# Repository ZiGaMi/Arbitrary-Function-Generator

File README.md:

# Arbitrary-Function-Generator
This repository contains of KiCad schematic and layout files, RTL code for iCE40 FPGA, C code for STM32F031K6 MCU and python script for software configuration of function generator.  

## Description
DAC: 12-bit R-2R ladder\
Output voltage: 3.3V\
SC current: 3.3mA

### Modes
Sinus: up to 1MHz\
Square: up to 100kHz\
Triange: up to 100kHz\
Saw: up to 100kHz\
Arbitrary: TBD

## Pics

work still in process...

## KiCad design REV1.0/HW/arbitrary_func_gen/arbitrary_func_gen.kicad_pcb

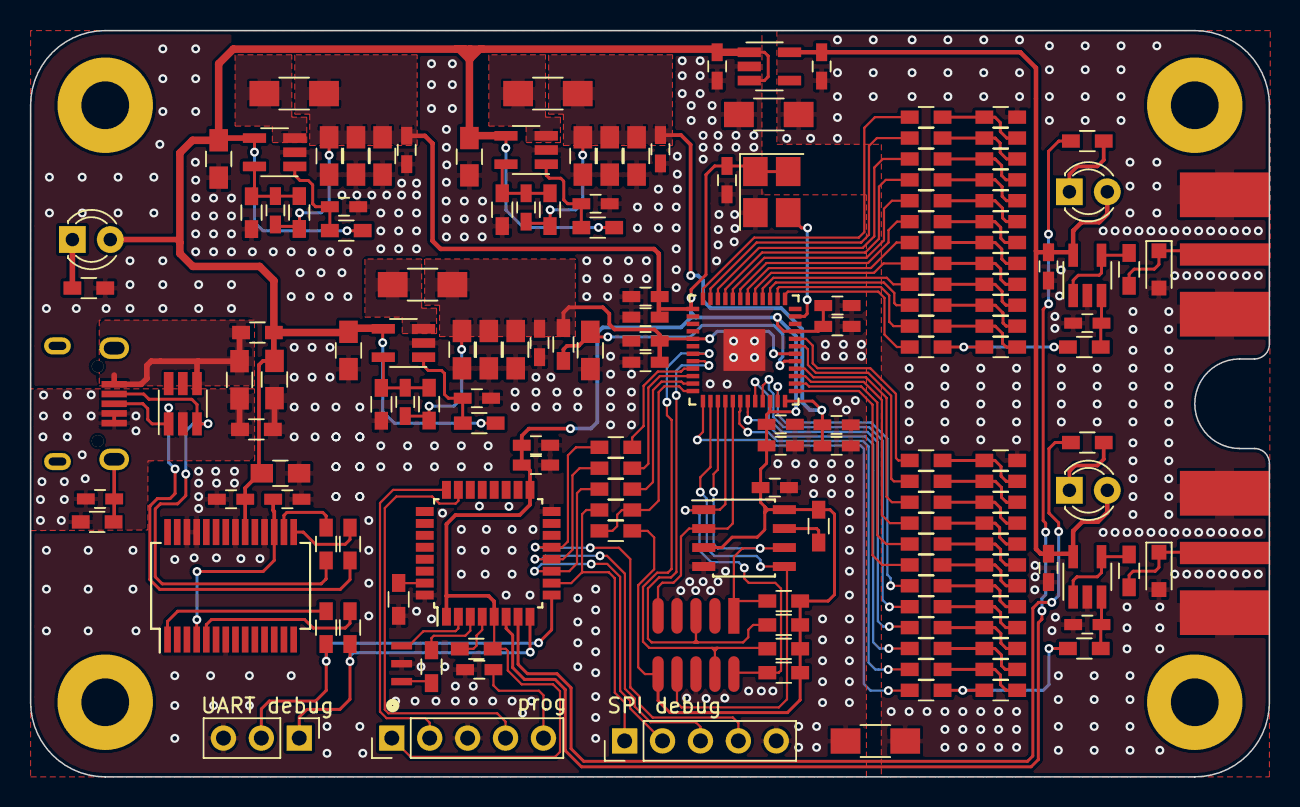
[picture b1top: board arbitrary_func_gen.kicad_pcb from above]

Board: 2 copper layers, 83.0 x 50.0 mm, 168 parts (0 on the bottom side), 111 nets.

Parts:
C1: 1n; C_0603_HandSoldering
C2, C3, C27, C46: 4u7; C_0805_HandSoldering
C4, C5, C15, C16, C17, C39, C49: 1u; C_0603_HandSoldering
C6, C7, C8, C18, C19, C20, C21, C22, C23, C24, C25, C26: 10u; C_0805_HandSoldering
C9, C12, C13, C14: DNS; C_0603_HandSoldering
C10, C11, C30, C31, C34, C35, C37, C40, C42, C44, C45, C47, C48: 100n; C_0603_HandSoldering
C28, C29, C32, C33, C36, C38, C41, C43: 10n; C_0603_HandSoldering
D1, D3, D4: LED; LED_D3.0mm_FlatTop
D2, D5: PESD3V3U1UA; D_SOD-323_HandSoldering
H1, H2, H3, H4: MountingHole_3.2mm_M3_Pad
J1: 629105150521_WE; USBMicro_629105150521_WE
J2: iCE40ProgPins; 2x5pin-R1.27mm
J3, J4: Conn_01x05; Pin_Header_Straight_1x05_Pitch2.54mm
J5, J6: SMA-J-P-H-ST-EM1; SMA_Coaxsial_EdgeBoard_Connector
J7: Conn_01x03; Pin_Header_Straight_1x03_Pitch2.54mm
L1, L2: BLM18PG471SH1D; L_0603_HandSoldering
L3, L4, L5: 2.2u; L_1206_HandSoldering
L6, L7: 22nH; L_0603_HandSoldering
R1: 1M; R_0603_HandSoldering
R2: 0R; R_1206_HandSoldering
R3: 0R; R_0603_HandSoldering
R4, R5, R13, R14, R15, R16, R17, R77: 10k; R_0603_HandSoldering
R6, R7, R8, R10: 150k; R_0603_HandSoldering
R9, R71, R72: 47k; R_0603_HandSoldering
R11: 33k; R_0603_HandSoldering
R12, R73, R74: 100R; R_0603_HandSoldering
R18, R43, R68, R75, R76, R78, R79, R80, R81: 1k; R_0603_HandSoldering
R19, R20, R21, R22, R23, R24, R25, R26, R27, R28, R29, R30, R42, R44, R45, R46, R47, R48, R49, R50, R51, R52, R53, R54, R55, R67: 22k; R_0603_HandSoldering
R31, R32, R33, R34, R35, R36, R37, R38, R39, R40, R41, R56, R57, R58, R59, R60, R61, R62, R63, R64, R65, R66: 11k; R_0603_HandSoldering
R69, R70: 27R; R_0603_HandSoldering
R82: DNS; R_1206_HandSoldering
R83: 680R; R_0603_HandSoldering
U1: IEC5LP1K-QFN48; QFP-48_7x7_Pitch0.5mm
U2: STM32F031K6Tx; LQFP-32_7x7mm_Pitch0.8mm
U3: FT232RL; SSOP-28_5.3x10.2mm_Pitch0.65mm
U4: LN1134; SOT-23-5_HandSoldering
U5, U7, U8: TLV62568DBV; SOT-23-5_HandSoldering
U6: SRV05-4; SOT-23-6_Handsoldering
U9: IS25LQ040B; SOIC-8_3.9x4.9mm_Pitch1.27mm
U10, U11: LT6220; SOT-23-5_HandSoldering
X1: ASFL1-25.000MHZ-EC-T; Oscillator_SMD_Abracon_ASE-4pin_3.2x2.5mm_HandSoldering
Y1: CSTCE8M00G15L99-R0; Crystal_Murata3Pin

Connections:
+1V2: C12.1, C15.1, C18.1, C21.1, C24.1, C29.1, C31.1, L3.2, R6.1, R12.2, U1.5, U1.30
+2V5: C13.1, C16.1, C19.1, C22.1, C25.1, C33.1, C35.1, L4.2, R8.1, U1.24
+3.3VA: C5.1, C40.1, C42.1, D3.2, D4.2, U4.5, U10.5, U11.5
+3V3: C14.1, C17.1, C20.1, C23.1, C26.1, C28.1, C30.1, C32.1, C34.1, C36.1, C37.1, C38.1, C39.2, C48.2, C49.2, J2.6, J3.1, L5.2, R10.1, R13.1, R14.1, R15.1, R16.1, R17.1, R71.1, R77.1, U1.1, U1.22, U1.33, U2.1, U2.5, U2.17, U9.3, U9.8, X1.1, X1.4
+5V: C3.1, C4.1, C6.1, C7.1, C8.1, C45.2, C46.2, D1.2, L1.2, R3.1, R4.1, R5.1, U3.20, U4.1, U4.3, U5.4, U7.4, U8.4
/FPGA/CDONE: J2.9, R13.2, U1.7
/FPGA/CLK_25MHZ: U1.35, X1.3
/FPGA/CRESET: J2.3, R14.2, U1.8
/FPGA/FLASH_CS: J2.10, R16.2, U1.16, U9.1
/FPGA/FLASH_MISO: J2.7, U1.14, U9.5
/FPGA/FLASH_MOSI: J2.5, U1.17, U9.2
/FPGA/FLASH_SCK: J2.1, R15.2, U1.15, U9.6
/MCU/CH1_LED: R78.2, U2.6
/MCU/CH2_LED: R79.2, U2.7
/MCU/CS_DBG: J4.1, R75.2, U2.10
/MCU/MISO_DBG: J4.3, R80.2, U2.12
/MCU/MOSI_DBG: J4.4, R81.2, U2.13
/MCU/NRST: C47.1, J3.5, R71.2, U2.4
/MCU/SCK_DBG: J4.2, R76.2, U2.11
/MCU/SWCLK: J3.2, U2.24
/MCU/SWDIO: J3.4, U2.23
/MCU/UART_RX: J7.2, R73.1, U2.9
/MCU/UART_TX: J7.1, R74.1, U2.8
BUSGND: C1.1, C2.2, J1.4, J1.5, L2.1, R1.2, U6.2
CH1_BIT_0: R30.2, U1.48
CH1_BIT_1: R29.2, U1.47
CH1_BIT_2: R28.2, U1.46
CH1_BIT_3: R27.2, U1.45
CH1_BIT_4: R26.2, U1.44
CH1_BIT_5: R25.2, U1.43
CH1_BIT_6: R24.2, U1.42
CH1_BIT_7: R23.2, U1.41
CH1_BIT_8: R22.2, U1.40
CH1_BIT_9: R21.2, U1.39
CH1_BIT_10: R20.2, U1.38
CH1_BIT_11: R19.2, U1.37
CH1_OUT: D2.1, J6.1, R43.1
CH2_BIT_0: R55.2, U1.32
CH2_BIT_1: R54.2, U1.31
CH2_BIT_2: R53.2, U1.28
CH2_BIT_3: R52.2, U1.27
CH2_BIT_4: R51.2, U1.26
CH2_BIT_5: R50.2, U1.25
CH2_BIT_6: R49.2, U1.23
CH2_BIT_7: R48.2, U1.21
CH2_BIT_8: R47.2, U1.20
CH2_BIT_9: R46.2, U1.19
CH2_BIT_10: R45.2, U1.18
CH2_BIT_11: R44.2, U1.13
CH2_OUT: D5.1, J5.1, R68.1
D+: J1.3, R69.1, U6.1
D-: J1.2, R70.1, U6.3
GND: C3.2, C4.2, C6.2, C7.2, C8.2, C9.2, C10.2, C11.2, C15.2, C16.2, C17.2, C18.2, C19.2, C20.2, C21.2, C22.2, C23.2, C24.2, C25.2, C26.2, C27.2, C28.2, C29.2, C30.2, C31.2, C32.2, C33.2, C34.2, C35.2, C36.2, C37.2, C38.2, C39.1, C44.1, C45.1, C46.1, C47.2, C48.1, C49.1, J2.4, J2.8, J3.3, J4.5, J7.3, L2.2, R2.2, R7.2, R9.2, R11.2, R18.2, R72.2, R82.2, U1.49, U2.16, U2.32, U3.7, U3.18, U3.21, U3.25, U3.26, U4.2, U5.2, U7.2, U8.2, U9.4, X1.2, Y1.2
GNDA: C5.2, C40.2, C41.2, C42.2, C43.2, D2.2, D5.2, J5.2, J6.2, R2.1, R42.2, R67.2, R82.1, U10.2, U11.2
MCU_CS: R75.1, R77.2, U1.12
MCU_MISO: R80.1, U1.10
MCU_MOSI: R81.1, U1.9
MCU_SCK: R76.1, U1.11
unnamed: C1.2, J1.6, R1.1
unnamed: C9.1, R3.2, U5.1
unnamed: C10.1, R4.2, U7.1
unnamed: C11.1, R5.2, U8.1
unnamed: C12.2, R6.2, R7.1, U5.5
unnamed: C13.2, R8.2, R9.1, U7.5
unnamed: C14.2, R10.2, R11.1, U8.5
unnamed: C41.1, L6.1, U10.3
unnamed: C43.1, L7.1, U11.3
unnamed: C44.2, U3.4, U3.17
unnamed: D1.1, R18.1
unnamed: D3.1, R78.1
unnamed: D4.1, R79.1
unnamed: L3.1, U5.3
unnamed: L4.1, U7.3
unnamed: L5.1, U8.3
unnamed: L6.2, R19.1, R31.1
unnamed: L7.2, R44.1, R56.1
unnamed: R17.2, U9.7
unnamed: R20.1, R31.2, R32.1
unnamed: R21.1, R32.2, R33.1
unnamed: R22.1, R33.2, R34.1
unnamed: R23.1, R34.2, R35.1
unnamed: R24.1, R35.2, R36.1
unnamed: R25.1, R36.2, R37.1
unnamed: R26.1, R37.2, R38.1
unnamed: R27.1, R38.2, R39.1
unnamed: R28.1, R39.2, R40.1
unnamed: R29.1, R40.2, R41.1
unnamed: R30.1, R41.2, R42.1
unnamed: R43.2, U10.1, U10.4
unnamed: R45.1, R56.2, R57.1
unnamed: R46.1, R57.2, R58.1
unnamed: R47.1, R58.2, R59.1
unnamed: R48.1, R59.2, R60.1
unnamed: R49.1, R60.2, R61.1
unnamed: R50.1, R61.2, R62.1
unnamed: R51.1, R62.2, R63.1
unnamed: R52.1, R63.2, R64.1
unnamed: R53.1, R64.2, R65.1
unnamed: R54.1, R65.2, R66.1
unnamed: R55.1, R66.2, R67.1
unnamed: R68.2, U11.1, U11.4
unnamed: R69.2, U3.15
unnamed: R70.2, U3.16
unnamed: R72.1, U2.31
unnamed: R73.2, U3.1
unnamed: R74.2, U3.5
unnamed: R83.1, U2.3
unnamed: R83.2, Y1.3
unnamed: U2.2, Y1.1
VBUS: C2.1, J1.1, L1.1, U6.4
VPLL: C27.1, R12.1, U1.29

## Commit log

2019-07-11 new file: REV1.0/HW/arbitrary_func_gen/arbitrary_func_gen.kicad_pcb new file: REV1.0/HW/arbitrary_func_gen/arbitrary_func_gen.pro new file: REV1.0/HW/arbitrary_func_gen/arbitrary_func_gen.sch
2019-07-13 new file: HW/arbitrary_func_gen/DAC.bak new file: HW/arbitrary_func_gen/DAC.sch new file: HW/arbitrary_func_gen/FPGA.bak new file: HW/arbitrary_func_gen/FPGA.sch new file: HW/arbitrary_func_gen/MCU.b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
2019-07-13 modified: HW/arbitrary_func_gen/DAC.bak modified: HW/arbitrary_func_gen/DAC.sch modified: HW/arbitrary_func_gen/Power.bak modified: HW/arbitrary_func_gen/Power.sch modified: HW/arbitrary_func_gen/arb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
2019-07-13 modified: HW/arbitrary_func_gen/FPGA.bak modified: HW/arbitrary_func_gen/FPGA.sch modified: HW/arbitrary_func_gen/Power.bak modified: HW/arbitrary_func_gen/Power.sch modified: HW/arbitrary_func_gen/a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
2019-07-20 modified: REV1.0/HW/arbitrary_func_gen/FPGA.bak modified: REV1.0/HW/arbitrary_func_gen/FPGA.sch modified: REV1.0/HW/arbitrary_func_gen/arbitrary_func_gen.bak modified: REV1.0/HW/arbitrary_func_gen/ar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
2019-07-20 modified: DAC.bak modified: DAC.sch modified: FPGA.bak modified: FPGA.sch modified: MCU.bak modified: MCU.sch modified: Power.bak modified: Power.sch modified: arbitrary_func_gen-cache.lib
2019-07-20 modified: HW/arbitrary_func_gen/MCU.bak modified: HW/arbitrary_func_gen/MCU.sch
2019-07-20 modified: HW/arbitrary_func_gen/DAC.bak modified: HW/arbitrary_func_gen/DAC.sch modified: HW/arbitrary_func_gen/FPGA.bak modified: HW/arbitrary_func_gen/FPGA.sch modified: HW/arbitrary_func_gen/MCU.b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
2019-07-23 modified: ../DAC.bak modified: ../DAC.sch modified: ../FPGA.bak modified: ../FPGA.sch new file: arbitrary_func_gen-F_Cu.pdf modified: ../MCU.bak modified: ../MCU.sch modified: ../Power.bak modified: 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
2019-07-24 modified: REV1.0/HW/arbitrary_func_gen/arbitrary_func_gen-cache.lib modified: REV1.0/HW/arbitrary_func_gen/arbitrary_func_gen.bak modified: REV1.0/HW/arbitrary_func_gen/arbitrary_func_gen.kicad_pcb n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
2019-07-24 modified: DAC.bak modified: DAC.sch modified: FPGA.bak modified: FPGA.sch modified: MCU.bak modified: MCU.sch modified: Power.bak modified: Power.sch modified: arbitrary_func_gen-cache.lib modified: 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
2019-07-24 modified: Power.sch new file: _autosave-Power.sch modified: arbitrary_func_gen.kicad_pcb modified: arbitrary_func_gen.kicad_pcb-bak modified: arbitrary_func_gen.net modified: fp-info-cache
2019-07-24 modified: arbitrary_func_gen/MCU.sch modified: arbitrary_func_gen/Power.bak deleted: arbitrary_func_gen/_autosave-Power.sch modified: arbitrary_func_gen/arbitrary_func_gen.kicad_pcb modified: arbitra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
2019-07-25 new file: DOCS/arbitrary_func_gen.pdf modified: HW/arbitrary_func_gen/DAC.bak modified: HW/arbitrary_func_gen/DAC.sch modified: HW/arbitrary_func_gen/FPGA.bak modified: HW/arbitrary_func_gen/FPGA.sch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
2019-07-25 modified: HW/arbitrary_func_gen/FPGA.bak modified: HW/arbitrary_func_gen/FPGA.sch modified: HW/arbitrary_func_gen/MCU.bak modified: HW/arbitrary_func_gen/MCU.sch modified: HW/arbitrary_func_gen/Power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
2019-07-26 modified: FPGA.bak modified: MCU.bak modified: MCU.sch modified: arbitrary_func_gen.kicad_pcb modified: arbitrary_func_gen.kicad_pcb-bak modified: arbitrary_func_gen.net modified: arbitrary_func_gen.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
2019-07-26 modified: MCU.bak modified: MCU.sch modified: arbitrary_func_gen-cache.lib modified: arbitrary_func_gen.kicad_pcb modified: arbitrary_func_gen.kicad_pcb-bak modified: arbitrary_func_gen.net modified: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
2019-07-27 modified: HW/arbitrary_func_gen/Power.bak modified: HW/arbitrary_func_gen/Power.sch modified: HW/arbitrary_func_gen/arbitrary_func_gen.kicad_pcb modified: HW/arbitrary_func_gen/arbitrary_func_gen.kic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
2019-07-27 deleted: REV1.0/HW/arbitrary_func_gen/Gerbers/arbitrary_func_gen-F_Cu.pdf modified: REV1.0/HW/arbitrary_func_gen/arbitrary_func_gen.kicad_pcb modified: REV1.0/HW/arbitrary_func_gen/arbitrary_func_gen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
2019-07-27 new file: SW/FunctionGenerator.py new file: SW/FunctionGeneratorProtocol.py
2019-07-27 deleted: ../DOCS/3d_pic.png deleted: ../HW/arbitrary_func_gen/Gerbers/arbitrary_fun_gen_rev1.0_gerbers.zip deleted: ../HW/arbitrary_func_gen/Gerbers/arbitrary_func_gen-B_Cu.gbr deleted: ../HW/arbitra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
2019-07-27 modified: ../DOCS/arbitrary_func_gen.pdf modified: ../HW/arbitrary_func_gen/arbitrary_func_gen.pro deleted: objdir/LOGICchain.vcd deleted: objdir/RT deleted: rebuild.py deleted: run.py
2019-07-27 modified: FunctionGenerator.v
2019-08-10 FunctionGeneratorDefines.py
2019-08-10 new file: src/Communication/DdsInterface.c new file: src/Communication/DdsInterface.h new file: src/Communication/PCInterface.c new file: src/Communication/PCInterface.h new file: src/Drivers/ClockDr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
2019-08-10 new file: REV1.0/SW/FunctionGeneratorDefines.py
2019-08-10 deleted: FW/src/Communication/DdsInterface.c deleted: FW/src/Communication/DdsInterface.h deleted: FW/src/Communication/PCInterface.c deleted: FW/src/Communication/PCInterface.h modified: FW/src/Driv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
2019-08-10 deleted: FW/.cproject deleted: FW/.gitignore deleted: FW/.project deleted: FW/.settings/org.eclipse.cdt.managedbuilder.core.prefs deleted: FW/src/Drivers/ClockDrv.c deleted: FW/src/Drivers/ClockDrv.h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
2019-08-10 new file: FW/Drivers/ClockDrv.c new file: FW/Drivers/ClockDrv.h new file: FW/Drivers/LedDrv.c new file: FW/Drivers/LedDrv.h new file: FW/main.c
2019-08-10 modified: main.c modified: ../HW/arbitrary_func_gen/fp-info-cache modified: ../SW/FunctionGenerator.py Communication/ Drivers/UartDrv.c Drivers/UartDrv.h
2019-08-10 new file: Communication/PcInterface.c new file: Communication/PcInterface.h new file: Drivers/UartDrv.c new file: Drivers/UartDrv.h
2019-08-12 new file: ClassicWaveforms.v modified: FunctionGenerator.v new file: SinusWaveform.v deleted: Waveform.v new file: WaveformClock.v new file: tb.v
2019-08-12 new file: Defines.vh modified: FunctionGenerator.v modified: SinusWaveform.v modified: WaveformClock.v
2019-08-13 modified: Defines.vh modified: SinusWaveform.v
2019-08-13 modified: FunctionGenerator.v modified: SinusWaveform.v
2019-08-13 new file: SinusLUTGenerator.py
2019-08-25 modified: Communication/PcInterface.c modified: Communication/PcInterface.h modified: Drivers/UartDrv.c modified: Drivers/UartDrv.h modified: main.c modified: tiny_printf.c modified: ../SW/SinusLUTGe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
2019-08-25 modified: Communication/PcInterface.c modified: Communication/PcInterface.h modified: Drivers/LedDrv.h modified: main.c modified: ../SW/FunctionGenerator.py
2019-08-26 modified: FunctionGenerator.py modified: FunctionGeneratorDefines.py modified: FunctionGeneratorProtocol.py
2019-08-26 modified: Communication/PcInterface.c modified: Communication/PcInterface.h modified: Drivers/UartDrv.h modified: main.c modified: ../SW/FunctionGenerator.py modified: ../SW/FunctionGeneratorDefines.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
2019-08-27 modified: Communication/PcInterface.c modified: Communication/PcInterface.h modified: Drivers/UartDrv.c modified: Drivers/UartDrv.h modified: main.c
2019-09-03 modified: REV1.0/SW/FunctionGenerator.py modified: REV1.0/SW/FunctionGeneratorDefines.py
2019-09-03 modified: Communication/PcInterface.c modified: Drivers/UartDrv.c modified: Drivers/UartDrv.h modified: main.c Drivers/SpiDrv.c Drivers/SpiDrv.h
2019-09-03 new file: SpiDrv.c new file: SpiDrv.h
2019-09-08 modified: Defines.vh modified: FunctionGenerator.v new file: Interface.v modified: SinusWaveform.v modified: tb.v
2019-09-08 modified: Defines.vh modified: Interface.v modified: tb.v
2019-09-10 modified: Defines.vh modified: FunctionGenerator.v modified: Interface.v modified: tb.v
2019-09-10 modified: Defines.vh modified: FunctionGenerator.v modified: Interface.v new file: RegisterFile.v modified: tb.v
2019-09-27 modified: Communication/PcInterface.c modified: Communication/PcInterface.h modified: Drivers/ClockDrv.c modified: Drivers/ClockDrv.h modified: Drivers/SpiDrv.c modified: Drivers/SpiDrv.h modified: D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
